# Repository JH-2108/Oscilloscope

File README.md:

# Oscilloscope
A compact, low-cost digital oscilloscope designed to visualize electrical signals in real time using a microcontroller and a display. 

The goal of this project is to build an affordable educational instrument that can sample low-voltage signals, displaying their waveforms, and provide a simple interface for observing basic electrical behavior. 

# Features 
- Real-time waveform visualization on a display
- Microcontroller-based analogue signal sampling
- voltage and time-scale indicators
- triggering for a more stable waveform display
- low-cost, accessible electronic components
- compact design with the potential for a custom enclosure

# Project goals 
- Develop a functional signal acquisition and waveform display system
- create a clear, usable interface for viewing electrical signals.
- document the entire process, check [journal](journal.md) to see it!

# Planned hardware components
| Component | Purpose |
|---|---|
| Microcontroller development board | Samples and processes the input signal | 
| Color display module | displays the waveforms and measurement information |
| input protection and conditioning circuit | Keeps input signals within safe operating limits |
| passive components | support signal conditioning and circuit operation | 
| user controls | adjust display and acquisition settings |
| prototyping hardware | supports circuit development and testing | 

# How this oscilloscope would work 
1. An input circuit receives a low-voltage electrical signal
2. The microcontroller samples the signal using its analogue-to-digital converter (ADC).
3. The firmware processes the samples and determines where to begin drawing the waveform.
4. The display renders the waveform against a time and voltage grid.
5. User controls adjust the viewing and acquisition settings where supported.

# Bill of Materials 

Will be inserted later

# Project pictures
**PCB design** 

**Schematics**

**3D renderred PCB design**

**3D render with enclosure**

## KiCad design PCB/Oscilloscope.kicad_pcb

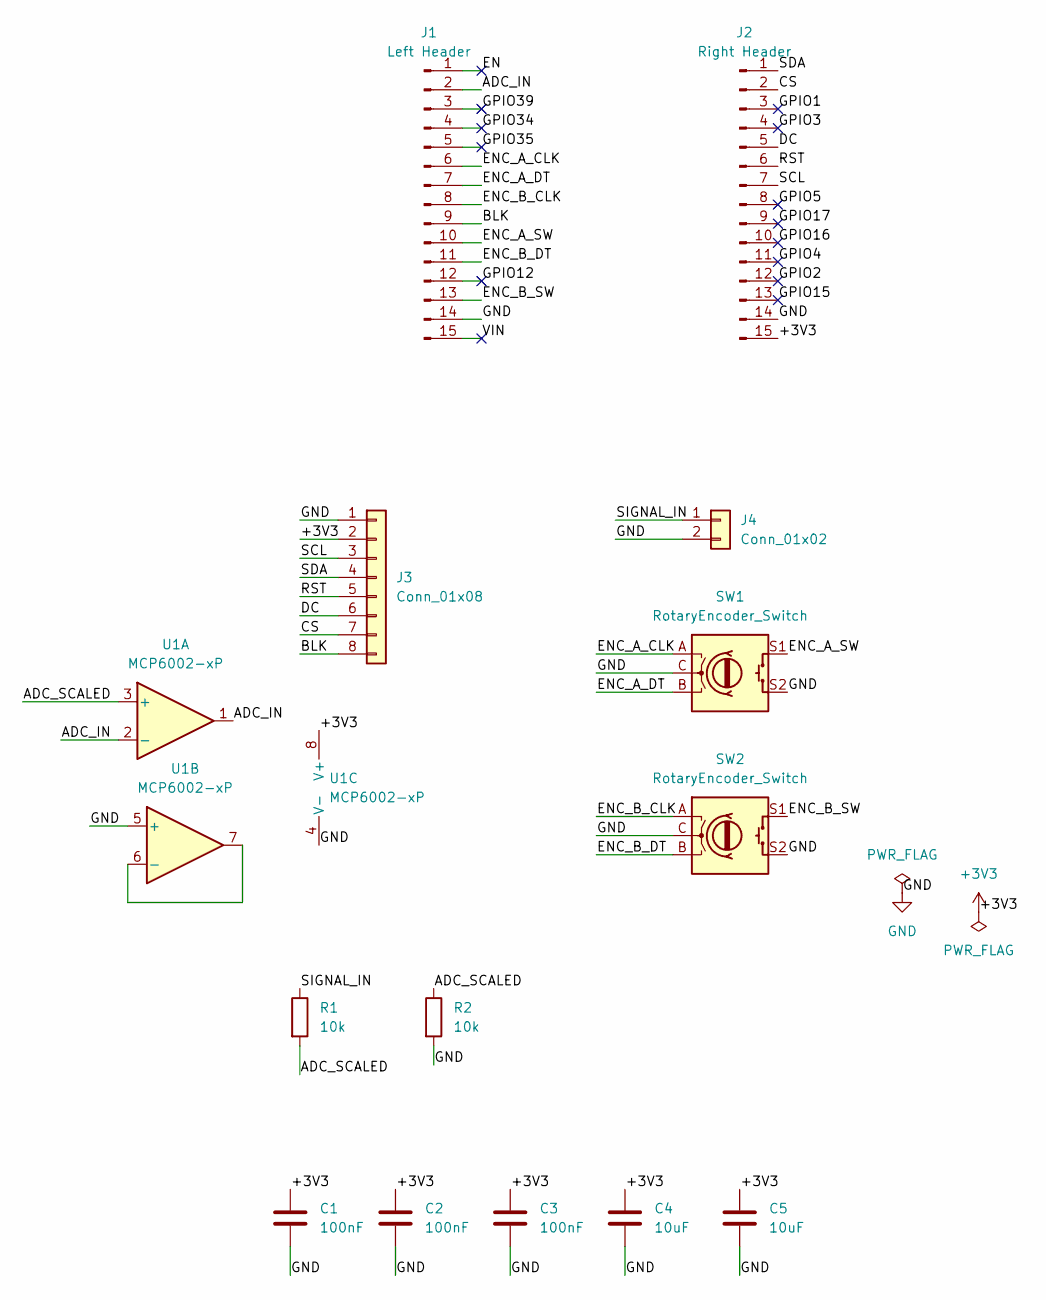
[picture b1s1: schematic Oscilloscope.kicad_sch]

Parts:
C1, C2, C3: 100nF; C_Disc_D5.0mm_W2.5mm_P5.00mm
C4, C5: 10uF; C_Disc_D5.0mm_W2.5mm_P5.00mm
J1: Left Header; PinSocket_1x15_P2.54mm_Vertical
J2: Right Header; PinSocket_1x15_P2.54mm_Vertical
J3: Conn_01x08; PinHeader_1x08_P2.54mm_Vertical
J4: Conn_01x02; TerminalBlock_Phoenix_MKDS-1,5-2-5.08_1x02_P5.08mm_Horizont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
R1, R2: 10k; R_Axial_DIN0207_L6.3mm_D2.5mm_P10.16mm_Horizontal
SW1, SW2: RotaryEncoder_Switch; RotaryEncoder_Alps_EC11E-Switch_Vertical_H20mm
U1: MCP6002-xP; DIP-8_W7.62mm

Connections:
+3V3: C1.1, C2.1, C3.1, C4.1, C5.1, J2.15, J3.2, U1.8 (V+)
/ADC_IN: J1.2, U1.1, U1.2 (-)
/ADC_SCALED: R1.2, R2.1, U1.3 (+)
/BLK: J1.9, J3.8
/CS: J2.2, J3.7
/DC: J2.5, J3.6
/EN: J1.1
/ENC_A_CLK: J1.6, SW1.A
/ENC_A_DT: J1.7, SW1.B
/ENC_A_SW: J1.10, SW1.S1
/ENC_B_CLK: J1.8, SW2.A
/ENC_B_DT: J1.11, SW2.B
/ENC_B_SW: J1.13, SW2.S1
/GPIO1: J2.3
/GPIO2: J2.12
/GPIO3: J2.4
/GPIO4: J2.11
/GPIO5: J2.8
/GPIO12: J1.12
/GPIO15: J2.13
/GPIO16: J2.10
/GPIO17: J2.9
/GPIO34: J1.4
/GPIO35: J1.5
/GPIO39: J1.3
/RST: J2.6, J3.5
/SCL: J2.7, J3.3
/SDA: J2.1, J3.4
/SIGNAL_IN: J4.1, R1.1
/VIN: J1.15
GND: C1.2, C2.2, C3.2, C4.2, C5.2, J1.14, J2.14, J3.1, J4.2, R2.2, SW1.C, SW1.S2, SW2.C, SW2.S2, U1.4 (V-), U1.5 (+)
unnamed: U1.6 (-), U1.7

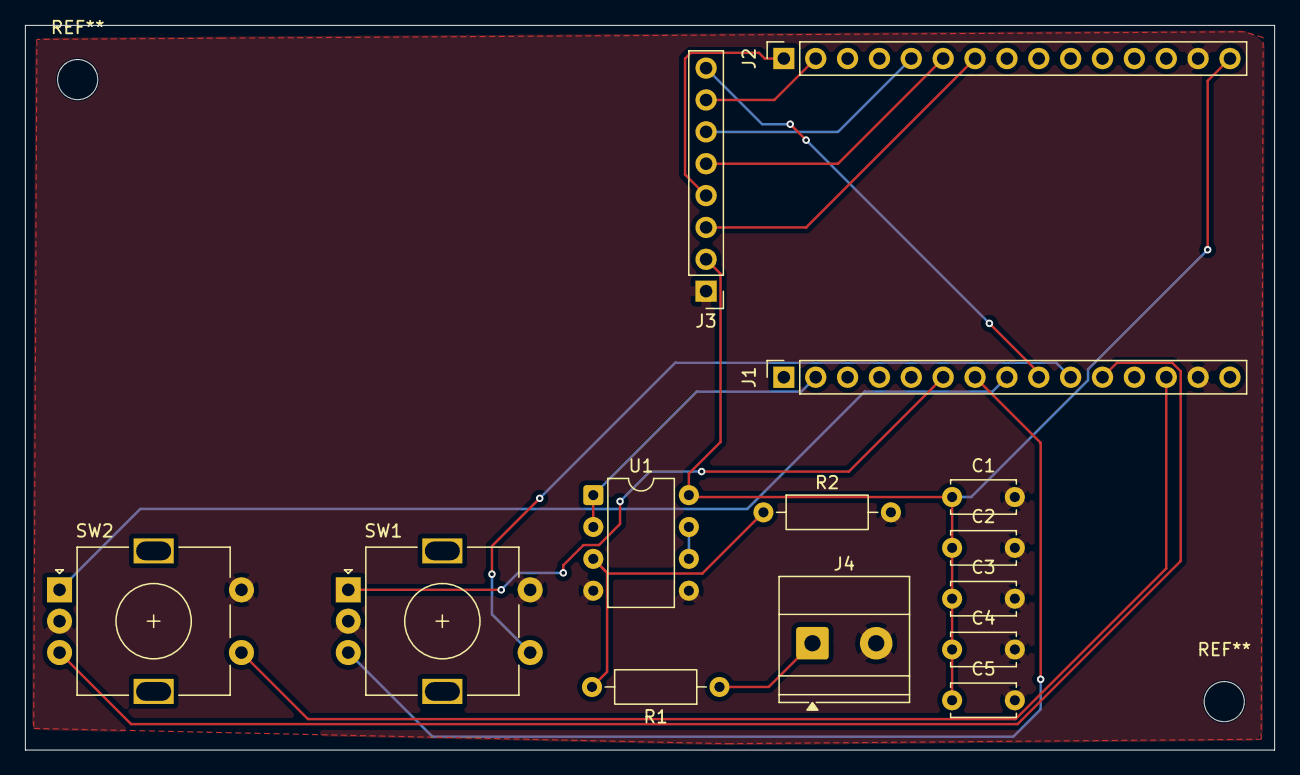
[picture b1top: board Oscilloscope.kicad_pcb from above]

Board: 2 copper layers, 99.6 x 57.8 mm, 14 parts (0 on the bottom side), 18 nets.

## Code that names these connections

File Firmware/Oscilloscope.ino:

#include <Arduino.h>
#include <SPI.h>
#include <Adafruit_GFX.h>
#include <Adafruit_ST7735.h>

constexpr int TFT_CS = 22; 
constexpr int TFT_DC = 21; 
constexpr int TFT_RST = 19; 
constexpr int TFT_SCLK = 18; 
constexpr int TFT_MOSI = 23; 
constexpr int TFT_BL = 26; 

//signal input 
constexpr int ADC_PIN = 36; 

//First encoder: timebase 
constexpr int ENC_A_CLK = 32; 
constexpr int ENC_A_DT = 33; 
constexpr int ENC_A_SW = 27; 

//Second encoder: vertical scale
constexpr int ENC_B_CLK = 25; 
constexpr int ENC_B_DT = 14; 
constexpr int ENC_B_SW = 13; 

Adafruit_ST7735 tft(TFT_CS, TFT_DC, TFT_RST);

//screen landscape size would be 160 x 128 
constexpr int SCREEN_W = 160; 
constexpr int SCREEN_H = 128; 

//waveform region on the screen
constexpr int X_LEFT = 8; 
constexpr int Y_TOP = 29; 
constexpr int Y_BOTTOM = 107; 
constexpr int WAVE_N = 144; 
constexpr int PLOT_H = Y_BOTTOM - Y_TOP;

const uint32_t sampleIntervals[] = {
    240, 500, 1000, 2000
}; 
constexpr int TIME_OPTIONS = 4;

const int verticalScales[] = {
    250, 500, 1000
}; 
constexpr int VOLT_OPTIONS = 3; 

int timeIndex = 2; 
int voltIndex = 2; 

bool running = true; 

uint16_t samples[WAVE_N]; 

int lastA = HIGH;
int lastB = HIGH
int positionA = 0; 
int positionB = 0; 
int appliedA = 0; 
int appliedB = 0; 

struct ButtonState { 
    int pin; 
    bool lastReading; 
    bool stableState; 
    uint32_t lastChange; 
}; 

ButtonState buttonA = {ENC_A_SW, HIGH, HIGH, 0};
ButtonState buttonB = {ENC_B_SW, HIGH, HIGH, 0};

bool buttonPressed(ButtonState &button) {
    bool reading = digitalRead(button.pin);
    uint32_t now = millis(); 

    if (reading != button.lastReading) { 
        button.lastChange = now; 
        button.lastReading = reading; 
    }

    if (now - button.lastChange  25 && reading != button.stableState) 
    {button.stableState = reading; 
        return button.stableState == LOW; 
    }

    return false;
}

void readEncoder(int pinA, int pinB, int &lastState, int &position) {
    int a = digitalRead(pinA);
    int b = digitalRead(pinB);

    if (a != lastState) { 
        if (a == b) {  
            posiiton++;
        } else {
            position--; 
        }
        lastState = a;
    }
}

void updateControls() {
    readEncoder(ENC_A_CLK, ENC_A_DT, lastA, positionA);
    readEncoder(ENC_B_CLK, ENC_B_DT, lastB, positionB);

    if (positionA != appliedA) {
        int change = positionA - appliedA; 
        timeIndex += change;
        timeIndex = constrain(timeIndex, 0, TIME_OPTIONS - 1); 
        appliedA = positionA; 
    }

    if (positionB != appliedB) {
        int change = positionB - appliedB; 
        voltIndex += change; 
        voltIndex = constrain(voltIndex, 0, VOLT_OPTIONS - 1);
        appliedB = positionB; 
    }

    if (buttonPressed(buttonA)) {
        running = !running; 
    }

    if (buttonpressed(buttonB)) {
        voltIndex = VOLT_OPTIONS - 1; 
        positinoB = 0; 
        appliedB = 0; 
    }
}

void captureWaveform() {
    uint32_t interval = sampleIntervals[timeIndex];

    for (int i = 0; i < WAVE_IN; i++) {
        uint32_t start = micros(); 

        uint32_t adcMv = analogReadMilliVolts(ADC_PIN); 

        uint32_t inputMv = adcMv * 2; 

        samples[i] = min(inputMv, (uint32_t)65535); 

        while ((uint32_t)(micros()-start) < interval) {
        }
    }
}

int voltageToY(uint16_t mv) {
    float fullScaleMv = verticalScales[voltIndex] * 6.0f; 

    int y = Y_BOTTOM - (int)((mv / fullScaleMv) * PLOT_H); 

    return constraint(y, Y_TOP, Y_BOTTOM); 
}

void drawGrid() {
    tft.fillRect(
        X_LEFT, Y_TOP, 145, PLOT_H + 1, ST77XX_BLACK
    );

    for (int i = 0; i <= 6; i++) {
        int y = Y_TOP + i * (PLOT_H / 6); 
        tft.drawFastHLine(
            X_LEFT, Y, 145, 0X4208
        );
    }

    for (int i = 0; i <= 8; i++) {
        int x = X_LEFT + i * 18; 
        tft.drawFastVLine(
            x, Y_TOP, PLOT_H + 1, 0X4208
        ); 
    }

    tft.drawRect(
        X_LEFT, Y_TOP, 145, PLOT_H + 1, ST77XX_WHITE
    ); 
}

void drawWaveform() { 
    for (int i = 1; i < WAVE_N; i++) {
        int x1 = X_LEFT + i - 1; 
        int x2 = X_LEFT + i; 

        int y1 = voltageToY(samples[i - 1]); 
        int y2 = voltageToY(samples[i]); 

        tft.drawLine(x1, y1, x2, y2, ST77XX_GREEN);
    }
}

void drawInterface() {
    tft.fillRect(0, 0, SCREEN_W, 27, ST77XX_BLACK);
    tft.fillRect(0, 110, SCREEN_W, 18, ST77XX_BLACK); 

    tft.setTextSize(1); 
    tft.setTextColor(ST77XX_WHITE, ST77XX_BLACK);
    tft.setCursor(3, 2);
    tft.print("Oscilloscope"); 

    float msPerDiv = sampleIntervals[timeIndex] * WAVE_N / 8.0f / 1000.0f;
    
    tft.setCursor(3, 15);
    tft.print(msPerDiv, 1); 
    tft.print("ms/div"); 

    tft.setCursor(87, 15); 
    tft.print(verticalScales[voltIndex] / 1000.0f, 2); 
    tft.pritn("V/div");

    tft.setCursor(3, 114); 
    tft.setTextColor(
        running ? ST77XX_GREEN: ST77XX_YELLOW, ST77XX_BLACK
    ); 
    tft.print(running ? "RUN" : "HOLD"); 

    tft.setTextColor(ST77XX_WHITE, ST77XX_BLACK); 
    tft.setCursor(43, 114); 
    tft.print("A:TIME B:VOLT"); 

    tft.setCursor(3, 122);
    tft.print("A click:RUN/HOLD B:RESET"); 
}

void setup() {
    Serial.begin(115200); 

    pinMode(TFT_BL, OUTPUT); 
    digitalWrite(TFT_BL, HIGH);

    pinMode(ENC_A_CLK, INPUT_PULLUP);
    pinmode(ENC_A_DT, INPUT_PULLUP);
    pinMode(ENC_A_SW, INPUT_PULLUP); 

    pinMode(ENC_B_CLK, INPUT_PULLUP);
    pinMode(ENC_B_DT, INPUT_PULLUP); 
    pinmode(ENC_B_SW, INPUT_PULLUP); 

    analogReadResolution(12); 
    analogSetPinAttenuation(ADC_PIN, ADC_6db); 

    SPI.begin(TFT_SCLK, -1, TFT_MOSI, TFT_CS); 

    tft.initR(INITR_BLACKTAB); 
    tft.setRotarion(1);
    tft.fillScreen(ST77XX_BLACK); 

    lastA = digitalRead(ENC_A_CLK);
    lastB = digitalRead(ENC_B_CLK); 

    for (int i = 0; i < WAVE_IN; i++) {
        samples[i] = 0; 
    }
    
    Serial.println("Shiiiii just turned onnnnnn")
} 

void loop() {
    updateControls(); 

    if (running) {
        captureWaveform(); 
    }

    drawInterface(); 
    drawGrid(); 
    drawWaveform(); 

    delay(10);
}
